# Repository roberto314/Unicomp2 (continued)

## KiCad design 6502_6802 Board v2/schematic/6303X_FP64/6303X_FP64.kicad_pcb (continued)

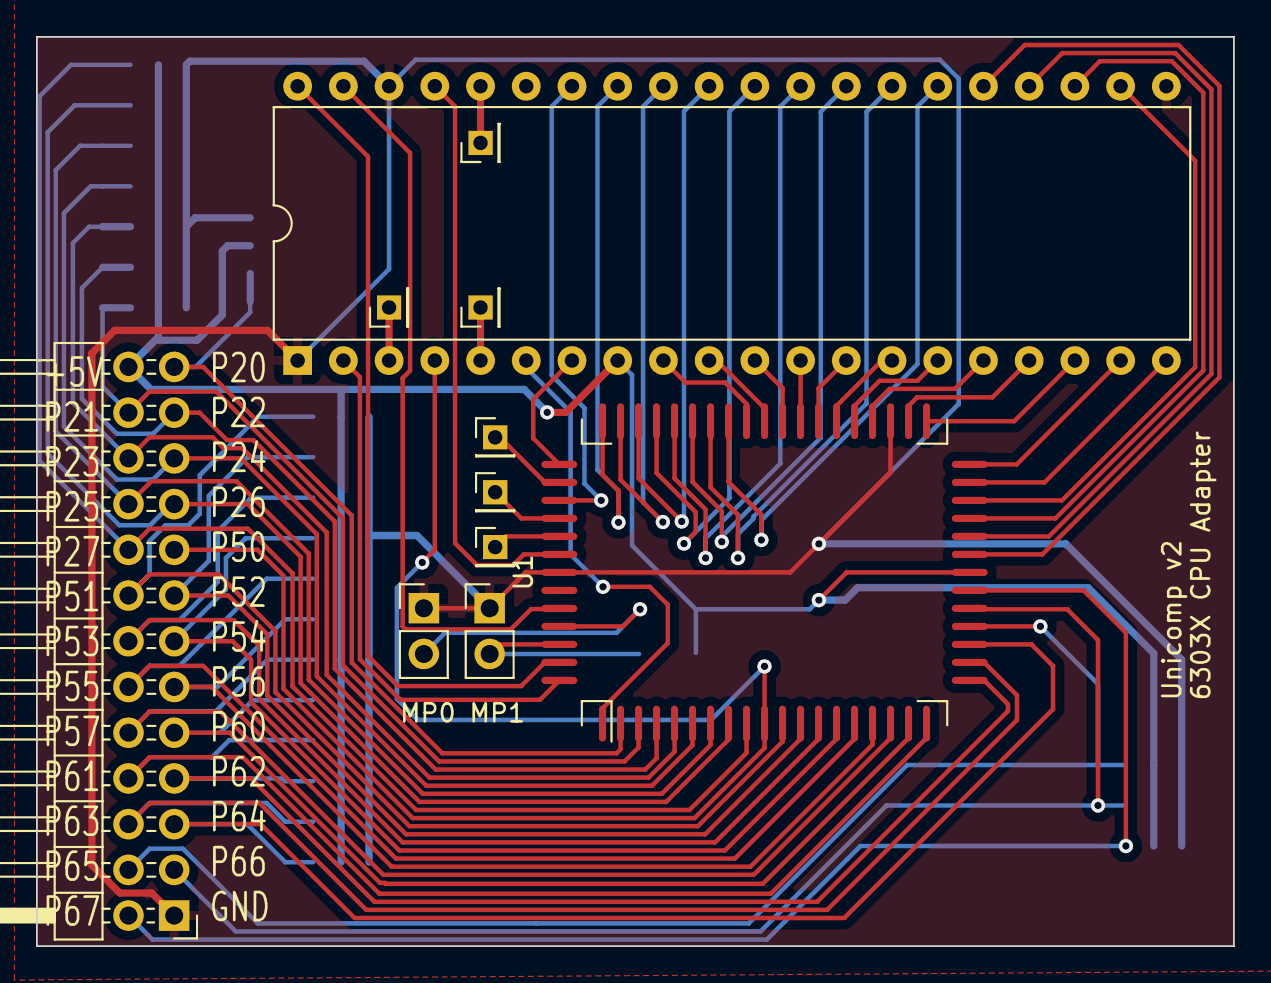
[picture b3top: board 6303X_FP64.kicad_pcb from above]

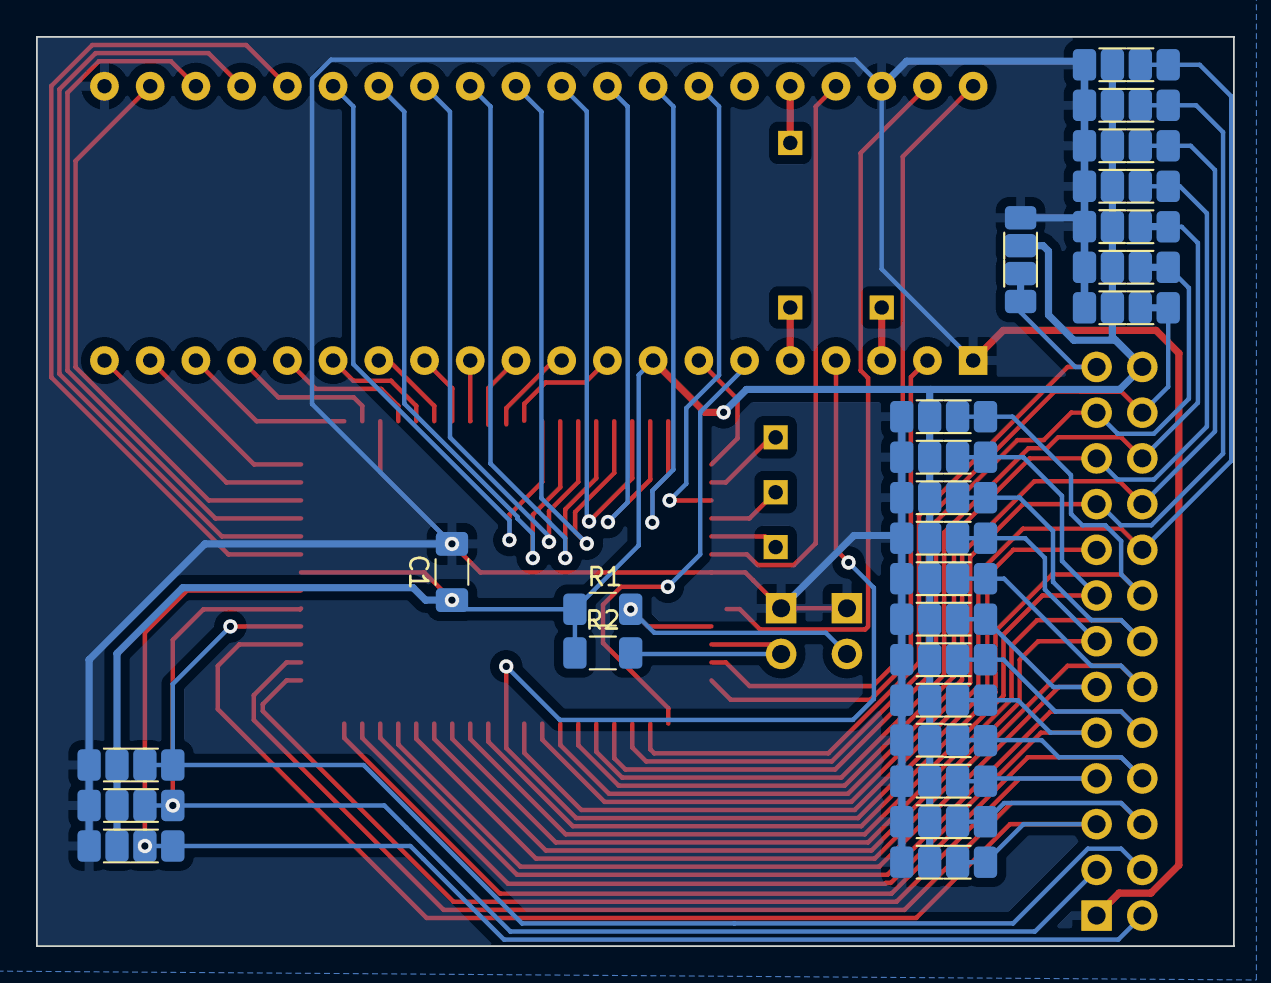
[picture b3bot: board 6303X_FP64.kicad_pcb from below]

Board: 2 copper layers, 66.5 x 50.5 mm, 60 parts (49 on the bottom side), 65 nets.

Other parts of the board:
U3: MC6802; DIP-40_W15.24mm

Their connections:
+5V: U3.8 (VCC); also elsewhere on the board
/A0: U3.9 (A0); also elsewhere on the board
/A1: U3.10 (A1); also elsewhere on the board
/A2: U3.11 (A2); also elsewhere on the board
/A3: U3.12 (A3); also elsewhere on the board
/A4: U3.13 (A4); also elsewhere on the board
/A5: U3.14 (A5); also elsewhere on the board
/A6: U3.15 (A6); also elsewhere on the board
/A7: U3.16 (A7); also elsewhere on the board
/A8: U3.17 (A8); also elsewhere on the board
/A9: U3.18 (A9); also elsewhere on the board
/A10: U3.19 (A10); also elsewhere on the board
/A11: U3.20 (A11); also elsewhere on the board
/A12: U3.22 (A12); also elsewhere on the board
/A13: U3.23 (A13); also elsewhere on the board
/A14: U3.24 (A14); also elsewhere on the board
/A15: U3.25 (A15); also elsewhere on the board
/BA: U3.7 (BA); also elsewhere on the board
/CPUCLK: U3.39 (EXTAL); also elsewhere on the board
/D0: U3.33 (D0); also elsewhere on the board
/D1: U3.32 (D1); also elsewhere on the board
/D2: U3.31 (D2); also elsewhere on the board
/D3: U3.30 (D3); also elsewhere on the board
/D4: U3.29 (D4); also elsewhere on the board
/D5: U3.28 (D5); also elsewhere on the board
/D6: U3.27 (D6); also elsewhere on the board
/D7: U3.26 (D7); also elsewhere on the board
/PHI2: U3.37 (E); also elsewhere on the board
/R/~W: U3.34 (R/~W); also elsewhere on the board
/~HALT: U3.2 (~HALT); also elsewhere on the board
/~IRQ1: U3.4 (~IRQ); also elsewhere on the board
/~NMI: U3.6 (~NMI); also elsewhere on the board
/~RST: U3.40 (~RESET); also elsewhere on the board
GND: U3.1 (VSS), U3.21 (VSS), U3.38 (XTAL); also elsewhere on the board
unnamed 63: U3.3 (MR); also elsewhere on the board
unnamed 64: U3.36 (RE); also elsewhere on the board
unnamed 65: U3.5 (VMA); also elsewhere on the board

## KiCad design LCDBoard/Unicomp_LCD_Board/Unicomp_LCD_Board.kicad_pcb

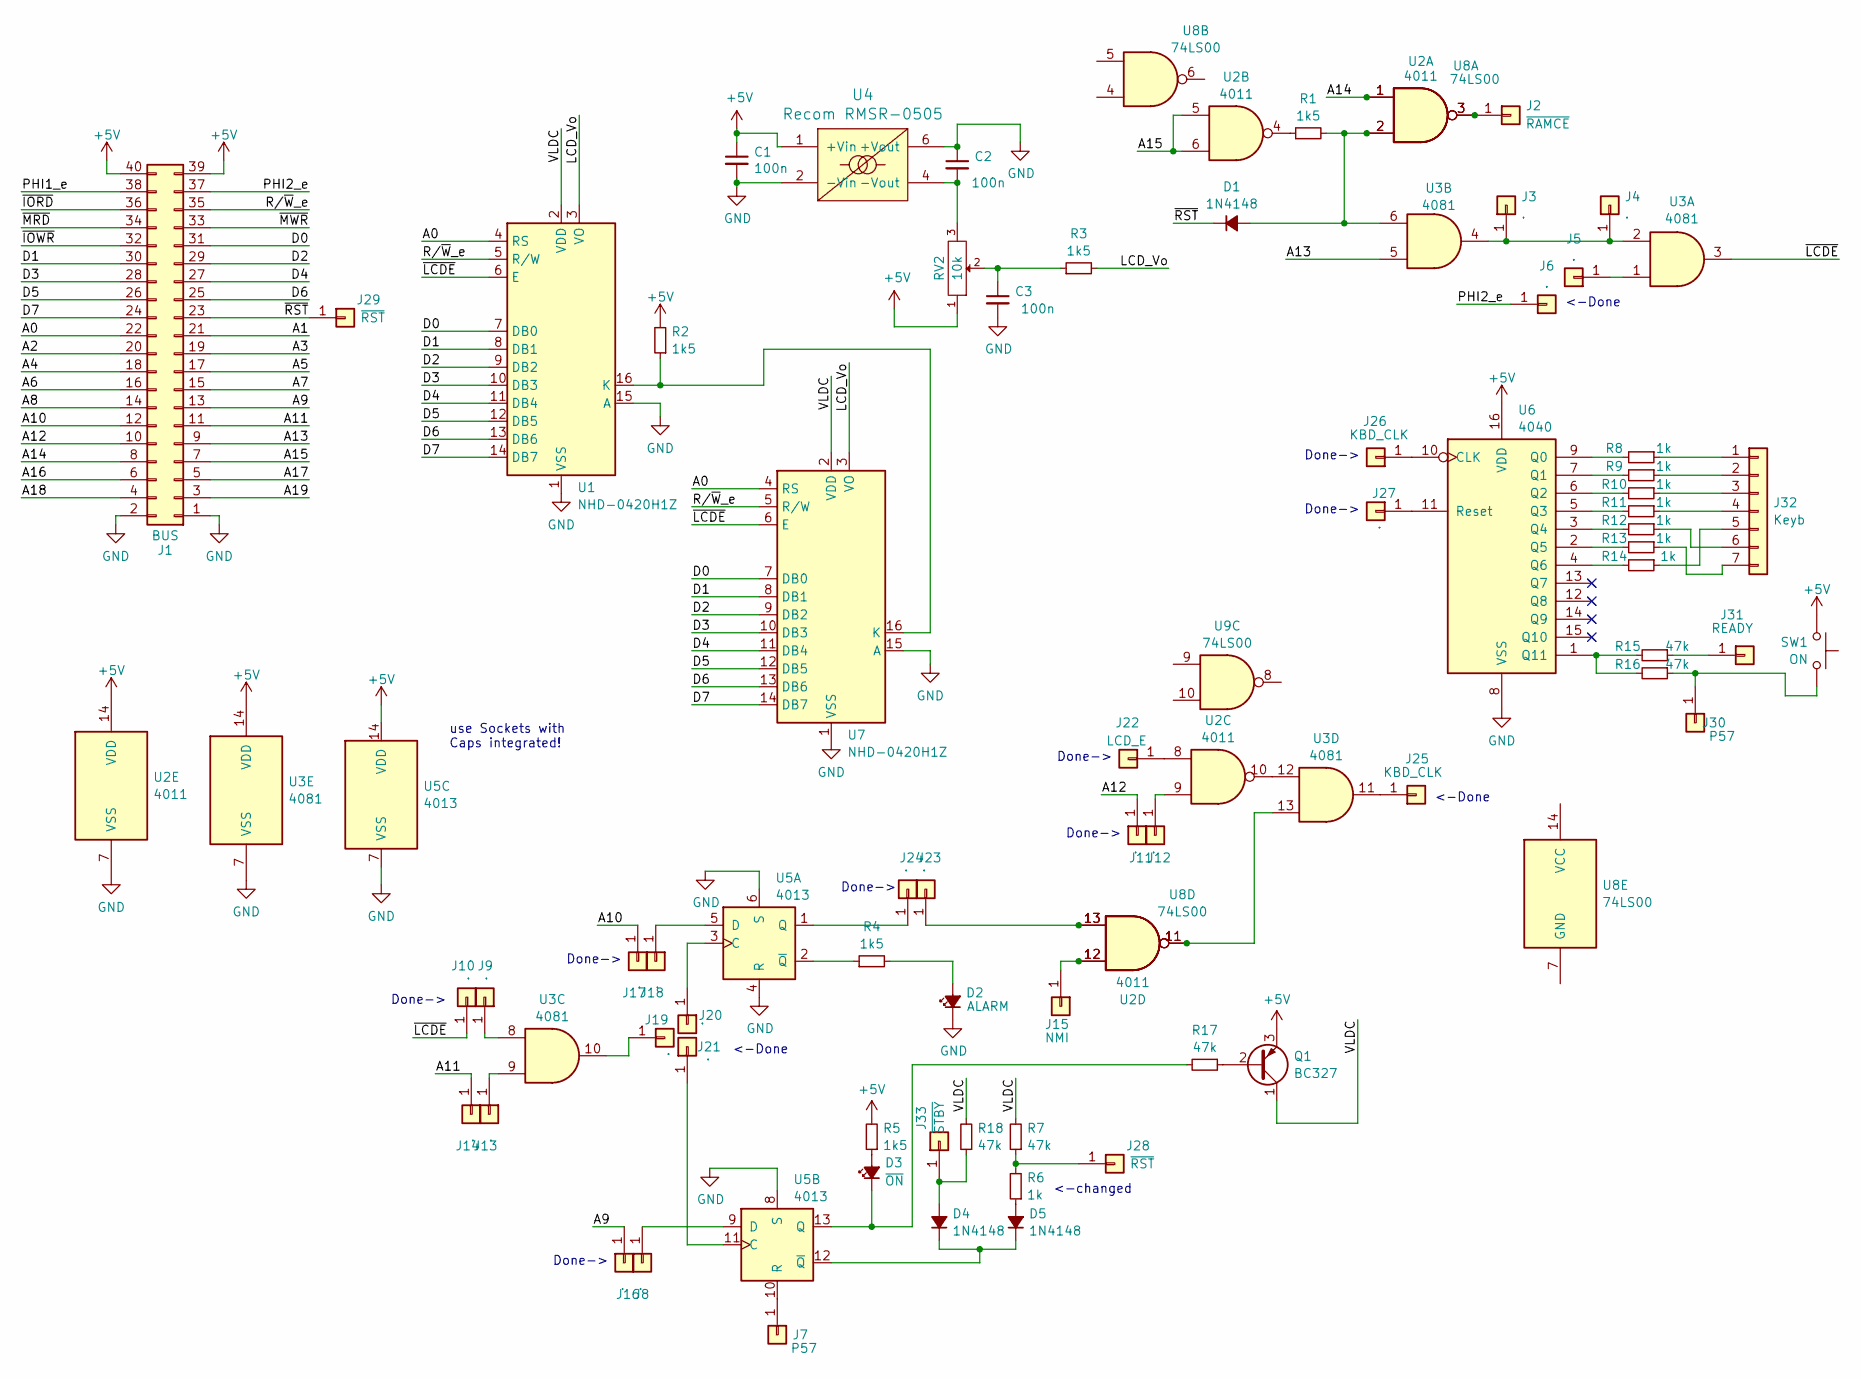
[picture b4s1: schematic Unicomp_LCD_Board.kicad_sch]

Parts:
C1, C2, C3: 100n; C_1206_3216Metric_Pad1.33x1.80mm_HandSolder
D1: 1N4148; D_A-405_P10.16mm_Horizontal
D2: ALARM; LED_D3.0mm
D3: ~{ON}; LED_D3.0mm
D4, D5: 1N4148; D_1206_3216Metric_Pad1.42x1.75mm_HandSolder
J1: BUS; PinHeader_2x20_P2.54mm_Horizontal
J2: ~{RAMCE}; PinHeader_1x01_P2.00mm_Vertical
J3, J4, J5, J6, J8, J9, J10, J11, J12, J13, J14, J16, J17, J18, J19, J20, J21, J23, J24, J27: .; PinHeader_1x01_P2.00mm_Vertical
J7, J30: P57; PinHeader_1x01_P2.00mm_Vertical
J15: NMI; PinHeader_1x01_P2.00mm_Vertical
J22: LCD_E; PinHeader_1x01_P2.00mm_Vertical
J25, J26: KBD_CLK; PinHeader_1x01_P2.00mm_Vertical
J28, J29: ~{RST}; PinHeader_1x01_P2.00mm_Vertical
J31: READY; PinHeader_1x01_P2.00mm_Vertical
J32: Keyb; PinHeader_1x07_P2.54mm_Vertical
J33: ~{STBY}; PinHeader_1x01_P2.00mm_Vertical
Q1: BC327; TO-92_Inline
R1: 1k5; R_Axial_DIN0207_L6.3mm_D2.5mm_P10.16mm_Horizontal
R2, R3, R4, R5: 1k5; R_1206_3216Metric_Pad1.30x1.75mm_HandSolder
R6, R8, R9, R10, R11, R12, R13, R14: 1k; R_1206_3216Metric_Pad1.30x1.75mm_HandSolder
R7, R15, R16, R17, R18: 47k; R_1206_3216Metric_Pad1.30x1.75mm_HandSolder
RV2: 10k; ALPS_RK09
SW1: ON; SW_PUSH_6mm
U1, U7: NHD-0420H1Z; PinSocket_1x16_P2.54mm_Vertical
U2: 4011; DIP-14_W7.62mm_Socket_LongPads
U3: 4081; DIP-14_W7.62mm_Socket_LongPads
U4: Recom RMSR-0505; Converter_DCDC_TRACO_TMR-1-xxxx_Dual_THT
U5: 4013; DIP-14_W7.62mm_Socket_LongPads
U6: 4040; DIP-16_W7.62mm_Socket_LongPads
U8, U9: 74LS00

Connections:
+5V: C1.1, J1.39, J1.40, Q1.3 (E), R2.2, R5.2, RV2.1, SW1.2, U2.14 (VDD), U3.14 (VDD), U4.1 (+Vin), U5.14 (VDD), U6.16 (VDD)
/A0: J1.22, U1.4 (RS), U7.4 (RS)
/A1: J1.21
/A2: J1.20
/A3: J1.19
/A4: J1.18
/A5: J1.17
/A6: J1.16
/A7: J1.15
/A8: J1.14
/A9: J1.13, J16.1
/A10: J1.12, J17.1
/A11: J1.11, J14.1
/A12: J1.10, J11.1
/A13: J1.9, U3.5
/A14: J1.8, U2.1, U8.1
/A15: J1.7, U2.5, U2.6
/A16: J1.6
/A17: J1.5
/A18: J1.4
/A19: J1.3
/D0: J1.31, U1.7 (DB0), U7.7 (DB0)
/D1: J1.30, U1.8 (DB1), U7.8 (DB1)
/D2: J1.29, U1.9 (DB2), U7.9 (DB2)
/D3: J1.28, U1.10 (DB3), U7.10 (DB3)
/D4: J1.27, U1.11 (DB4), U7.11 (DB4)
/D5: J1.26, U1.12 (DB5), U7.12 (DB5)
/D6: J1.25, U1.13 (DB6), U7.13 (DB6)
/D7: J1.24, U1.14 (DB7), U7.14 (DB7)
/LCD_Vo: R3.2, U1.3 (VO), U7.3 (VO)
/PHI1_e: J1.38
/PHI2_e: J1.37, J6.1
/R/~W_e: J1.35, U1.5 (R/W), U7.5 (R/W)
/VLDC: Q1.1 (C), R7.2, R18.2, U1.2 (VDD), U7.2 (VDD)
/~IORD: J1.36
/~IOWR: J1.32
/~LCDE: J10.1, U1.6 (E), U3.3, U7.6 (E)
/~MRD: J1.34
/~MWR: J1.33
/~RST: D1.1 (K), J1.23, J29.1
GND: C1.2, C2.1, C3.2, D2.1 (K), J1.1, J1.2, U1.1 (VSS), U1.15 (A), U2.7 (VSS), U3.7 (VSS), U4.2 (-Vin), U4.6 (+Vout), U5.4 (R), U5.6 (S), U5.7 (VSS), U5.8 (S), U6.8 (VSS), U7.1 (VSS), U7.15 (A)
unnamed: C3.1, R3.1, RV2.2
unnamed: D1.2 (A), R1.2, U2.2, U3.6, U8.2
unnamed: D2.2 (A), R4.2
unnamed: D3.2 (A), R5.1
unnamed: D3.1 (K), R17.2, U5.13 (Q)
unnamed: D4.2 (A), J33.1, R18.1
unnamed: D4.1 (K), D5.1 (K), U5.12 (~Q)
unnamed: D5.2 (A), R6.1
unnamed: J2.1, U2.3, U8.3
unnamed: J3.1, J4.1, U3.2, U3.4
unnamed: J5.1, U3.1
unnamed: J7.1, U5.10 (R)
unnamed: J8.1, U5.9 (D)
unnamed: J9.1, U3.8
unnamed: J12.1, U2.9
unnamed: J13.1, U3.9
unnamed: J15.1, U2.12, U8.12
unnamed: J18.1, U5.5 (D)
unnamed: J19.1, U3.10
unnamed: J20.1, U5.3 (C)
unnamed: J21.1, U5.11 (C)
unnamed: J22.1, U2.8
unnamed: J23.1, U2.13, U8.13
unnamed: J24.1, U5.1 (Q)
unnamed: J25.1, U3.11
unnamed: J26.1, U6.10 (CLK)
unnamed: J27.1, U6.11 (Reset)
unnamed: J28.1, R6.2, R7.1
unnamed: J30.1, R16.1, SW1.1
unnamed: J31.1, R15.1
unnamed: J32.1, R8.1
unnamed: J32.2, R9.1
unnamed: J32.3, R10.1
unnamed: J32.4, R11.1
unnamed: J32.5, R14.1
unnamed: J32.6, R12.1
unnamed: J32.7, R13.1
unnamed: Q1.2 (B), R17.1
unnamed: R1.1, U2.4
unnamed: R2.1, U1.16 (K), U7.16 (K)
unnamed: U2.10, U3.12
unnamed: U2.11, U3.13, U8.11
unnamed: C2.2, RV2.3, U4.4 (-Vout)
unnamed: R4.1, U5.2 (~Q)
unnamed: R8.2, U6.9 (Q0)
unnamed: R9.2, U6.7 (Q1)
unnamed: R10.2, U6.6 (Q2)
unnamed: R11.2, U6.5 (Q3)
unnamed: R12.2, U6.3 (Q4)
unnamed: R13.2, U6.2 (Q5)
unnamed: R14.2, U6.4 (Q6)
unnamed: R15.2, R16.2, U6.1 (Q11)

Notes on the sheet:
<-Done
Done->
use Sockets with Caps integrated!
<-changed

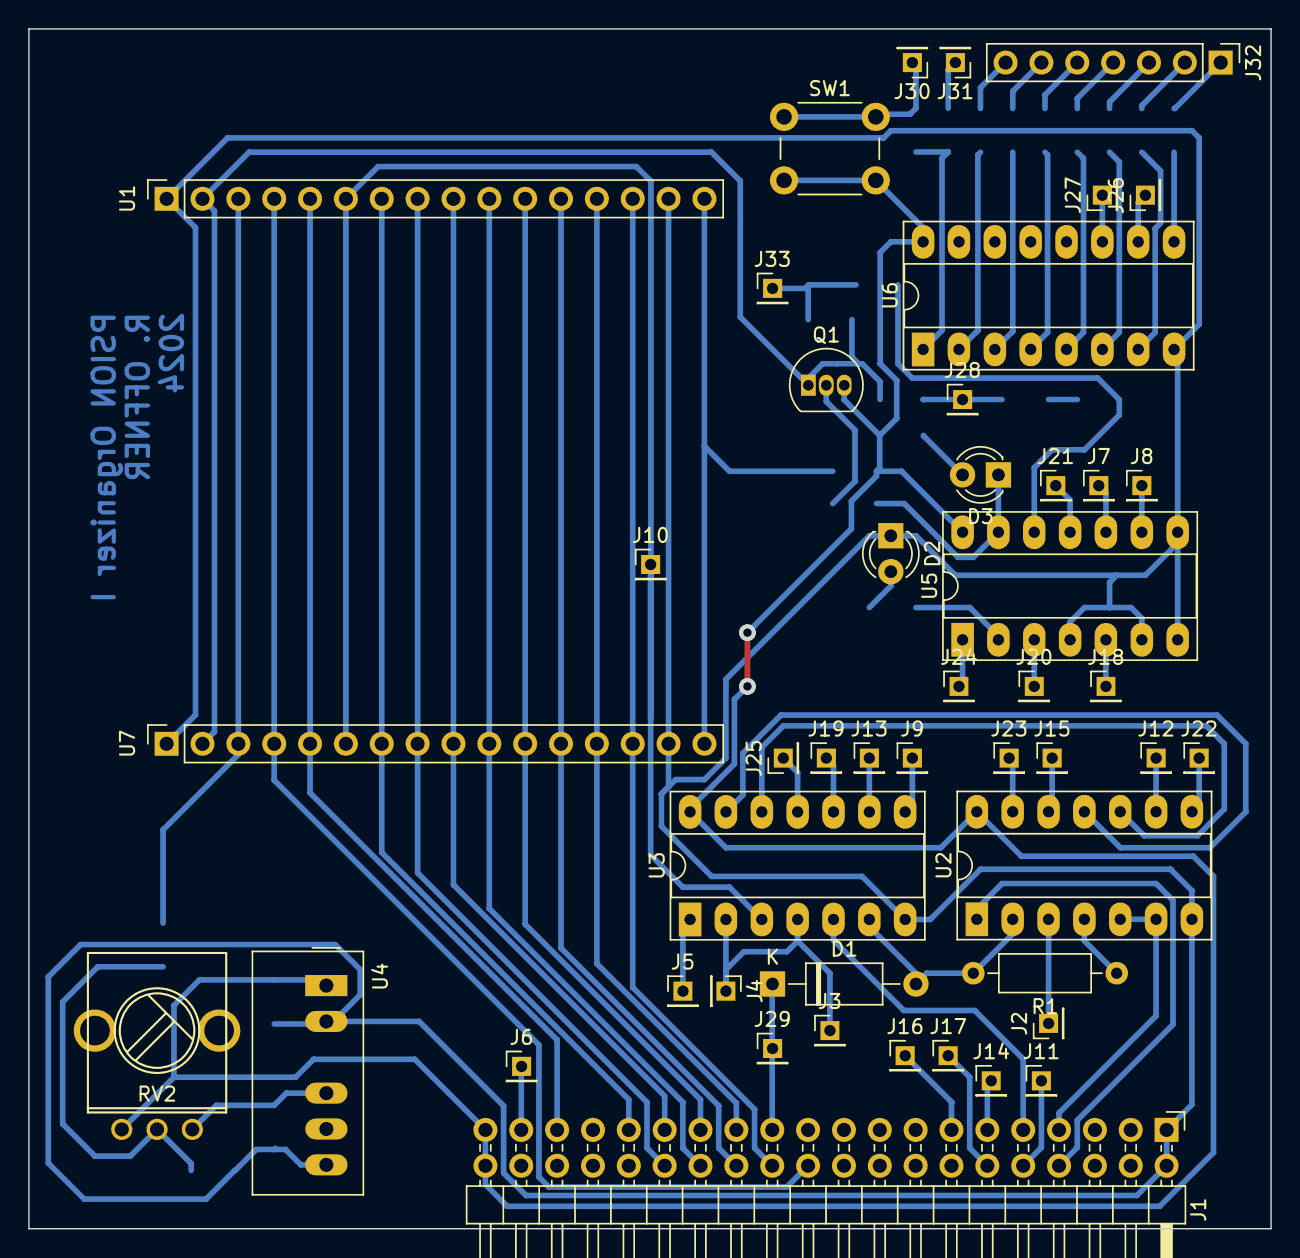
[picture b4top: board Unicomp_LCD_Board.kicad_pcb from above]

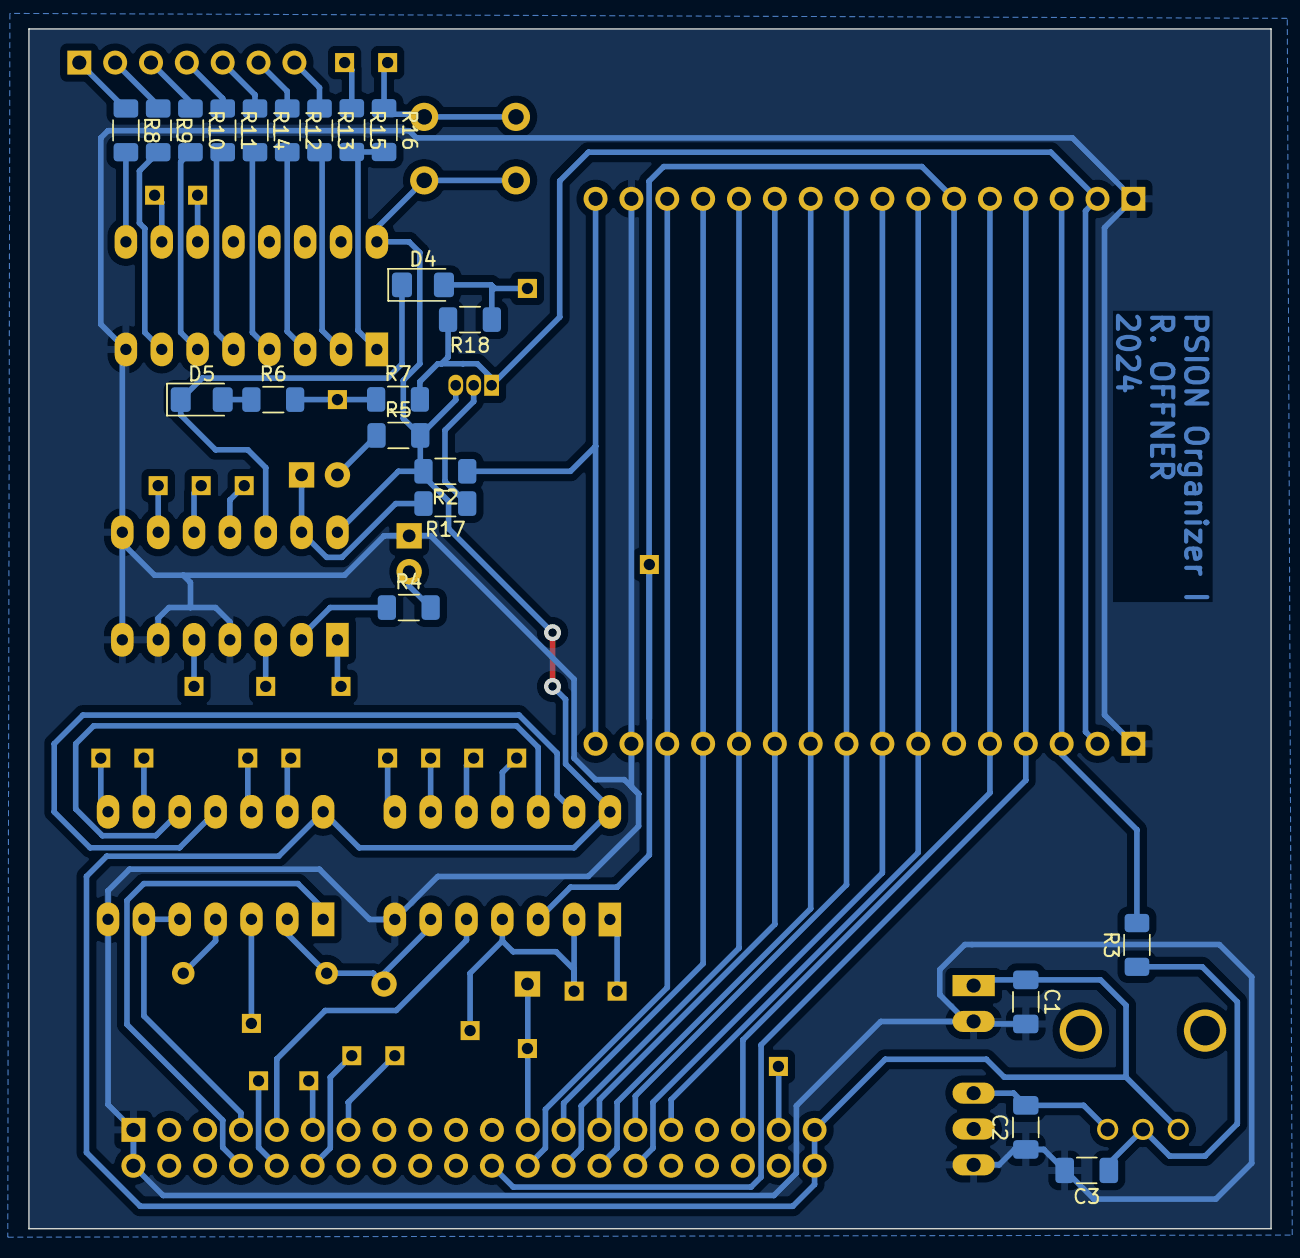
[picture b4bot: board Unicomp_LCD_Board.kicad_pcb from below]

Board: 2 copper layers, 88.0 x 85.0 mm, 69 parts (22 on the bottom side), 76 nets.

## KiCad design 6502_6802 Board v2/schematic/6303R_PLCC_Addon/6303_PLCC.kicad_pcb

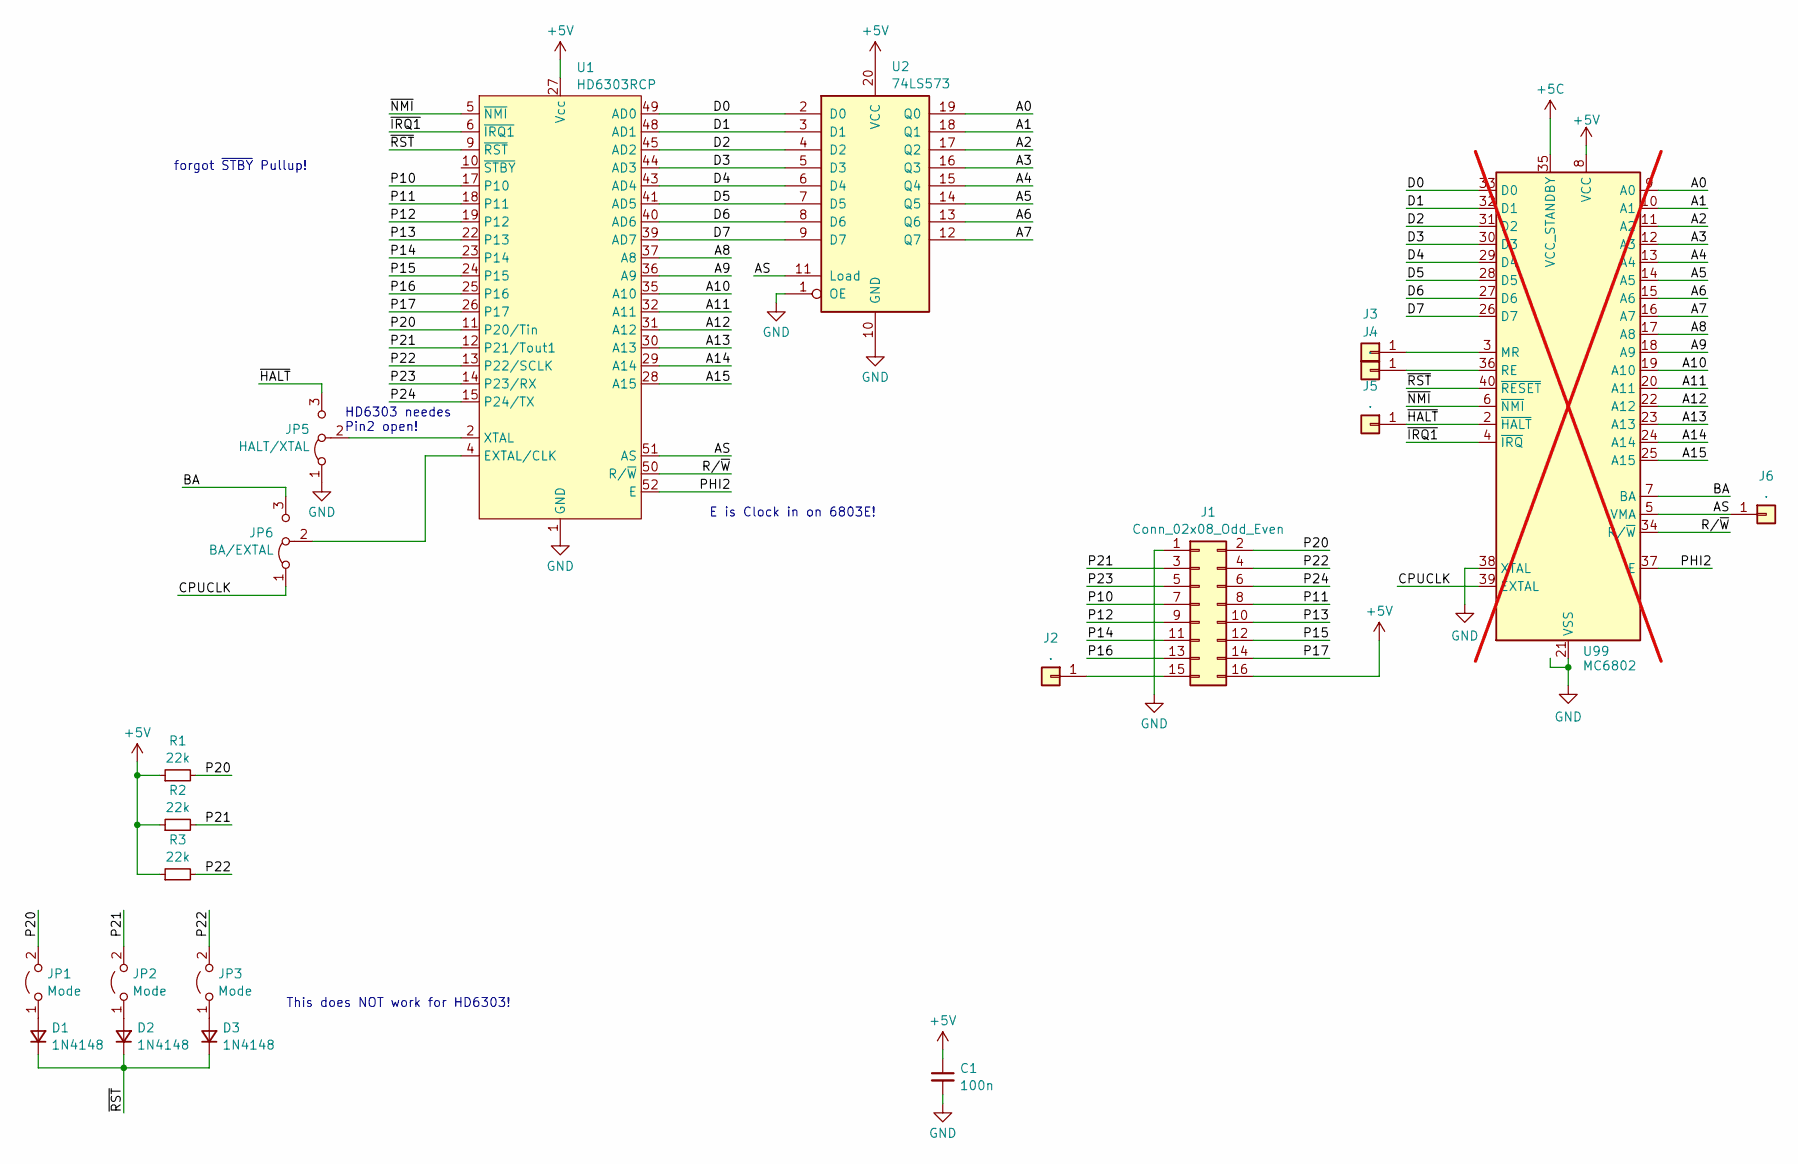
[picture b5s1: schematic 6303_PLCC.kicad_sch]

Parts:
C1: 100n; C_1206_3216Metric_Pad1.33x1.80mm_HandSolder
D1, D2, D3: 1N4148; D_1206_3216Metric_Pad1.42x1.75mm_HandSolder
J1: Conn_02x08_Odd_Even; PinHeader_2x08_P2.54mm_Horizontal
J2, J3, J4, J5, J6: .; PinHeader_1x01_P2.00mm_Vertical
JP1, JP2, JP3: Mode; PinHeader_1x02_P2.54mm_Vertical
JP5: HALT/XTAL; PinHeader_1x03_P2.54mm_Vertical
JP6: BA/EXTAL; PinHeader_1x03_P2.54mm_Vertical
R1, R2, R3: 22k; R_1206_3216Metric_Pad1.30x1.75mm_HandSolder
U1: HD6303RCP; PLCC-52_SMD-Socket
U2: 74LS573; DIP-20_W7.62mm_Socket_LongPads
U99: MC6802; DIP-40_W15.24mm; not fitted

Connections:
+5V: C1.1, J1.16, R1.1, R2.1, R3.1, U1.27 (Vcc), U2.20 (VCC); also elsewhere on the board
/A0: U2.19 (Q0); also elsewhere on the board
/A1: U2.18 (Q1); also elsewhere on the board
/A2: U2.17 (Q2); also elsewhere on the board
/A3: U2.16 (Q3); also elsewhere on the board
/A4: U2.15 (Q4); also elsewhere on the board
/A5: U2.14 (Q5); also elsewhere on the board
/A6: U2.13 (Q6); also elsewhere on the board
/A7: U2.12 (Q7); also elsewhere on the board
/A8: U1.37 (A8); also elsewhere on the board
/A9: U1.36 (A9); also elsewhere on the board
/A10: U1.35 (A10); also elsewhere on the board
/A11: U1.32 (A11); also elsewhere on the board
/A12: U1.31 (A12); also elsewhere on the board
/A13: U1.30 (A13); also elsewhere on the board
/A14: U1.29 (A14); also elsewhere on the board
/A15: U1.28 (A15); also elsewhere on the board
/AS: J6.1, U1.51 (AS), U2.11 (Load); also elsewhere on the board
/BA: JP6.3 (B); also elsewhere on the board
/CPUCLK: JP6.1 (A); also elsewhere on the board
/D0: U1.49 (AD0), U2.2 (D0); also elsewhere on the board
/D1: U1.48 (AD1), U2.3 (D1); also elsewhere on the board
/D2: U1.45 (AD2), U2.4 (D2); also elsewhere on the board
/D3: U1.44 (AD3), U2.5 (D3); also elsewhere on the board
/D4: U1.43 (AD4), U2.6 (D4); also elsewhere on the board
/D5: U1.41 (AD5), U2.7 (D5); also elsewhere on the board
/D6: U1.40 (AD6), U2.8 (D6); also elsewhere on the board
/D7: U1.39 (AD7), U2.9 (D7); also elsewhere on the board
/P10: J1.7, U1.17 (P10)
/P11: J1.8, U1.18 (P11)
/P12: J1.9, U1.19 (P12)
/P13: J1.10, U1.22 (P13)
/P14: J1.11, U1.23 (P14)
/P15: J1.12, U1.24 (P15)
/P16: J1.13, U1.25 (P16)
/P17: J1.14, U1.26 (P17)
/P20: J1.2, JP1.2 (B), R1.2, U1.11 (P20/Tin)
/P21: J1.3, JP2.2 (B), R2.2, U1.12 (P21/Tout1)
/P22: J1.4, JP3.2 (B), R3.2, U1.13 (P22/SCLK)
/P23: J1.5, U1.14 (P23/RX)
/P24: J1.6, U1.15 (P24/TX)
/PHI2: U1.52 (E); also elsewhere on the board
/R/~W: U1.50 (R/~W); also elsewhere on the board
/~HALT: J5.1, JP5.3 (B); also elsewhere on the board
/~IRQ1: U1.6 (~IRQ1); also elsewhere on the board
/~NMI: U1.5 (~NMI); also elsewhere on the board
/~RST: D1.1 (K), D2.1 (K), D3.1 (K), U1.9 (~RST); also elsewhere on the board
GND: C1.2, J1.1, JP5.1 (A), U1.1 (GND), U2.1 (OE), U2.10 (GND); also elsewhere on the board
unnamed: D1.2 (A), JP1.1 (A)
unnamed: D2.2 (A), JP2.1 (A)
unnamed: D3.2 (A), JP3.1 (A)
unnamed: J1.15, J2.1
unnamed 53: J3.1; also elsewhere on the board
unnamed 54: J4.1; also elsewhere on the board
unnamed: JP5.2 (C), U1.2 (XTAL)
unnamed: JP6.2 (C), U1.4 (EXTAL/CLK)

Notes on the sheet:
forgot ~{STBY} Pullup!
This does NOT work for HD6303!
E is Clock in on 6803E!
HD6303 needes Pin2 open!

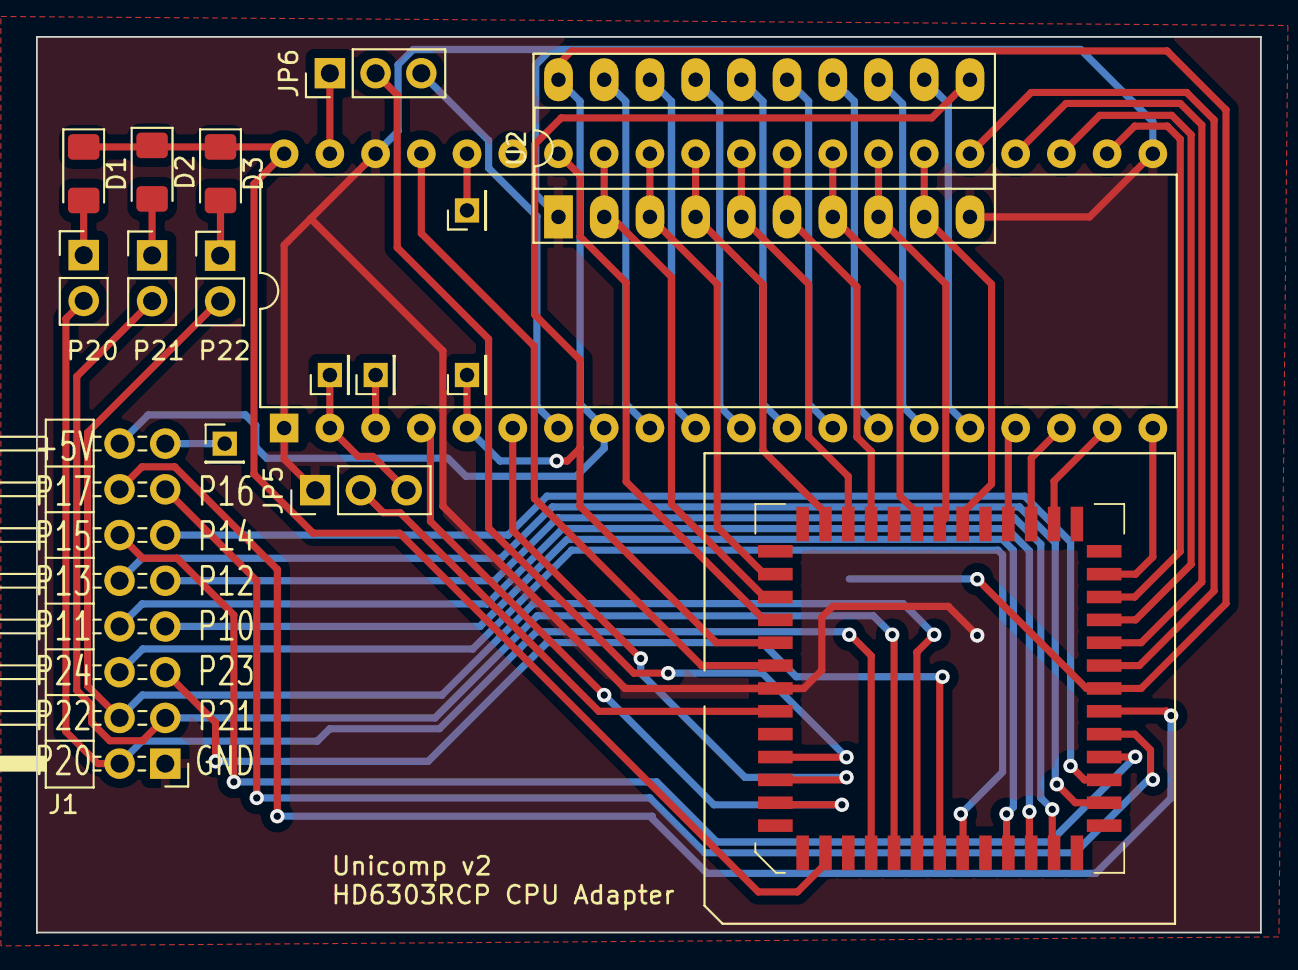
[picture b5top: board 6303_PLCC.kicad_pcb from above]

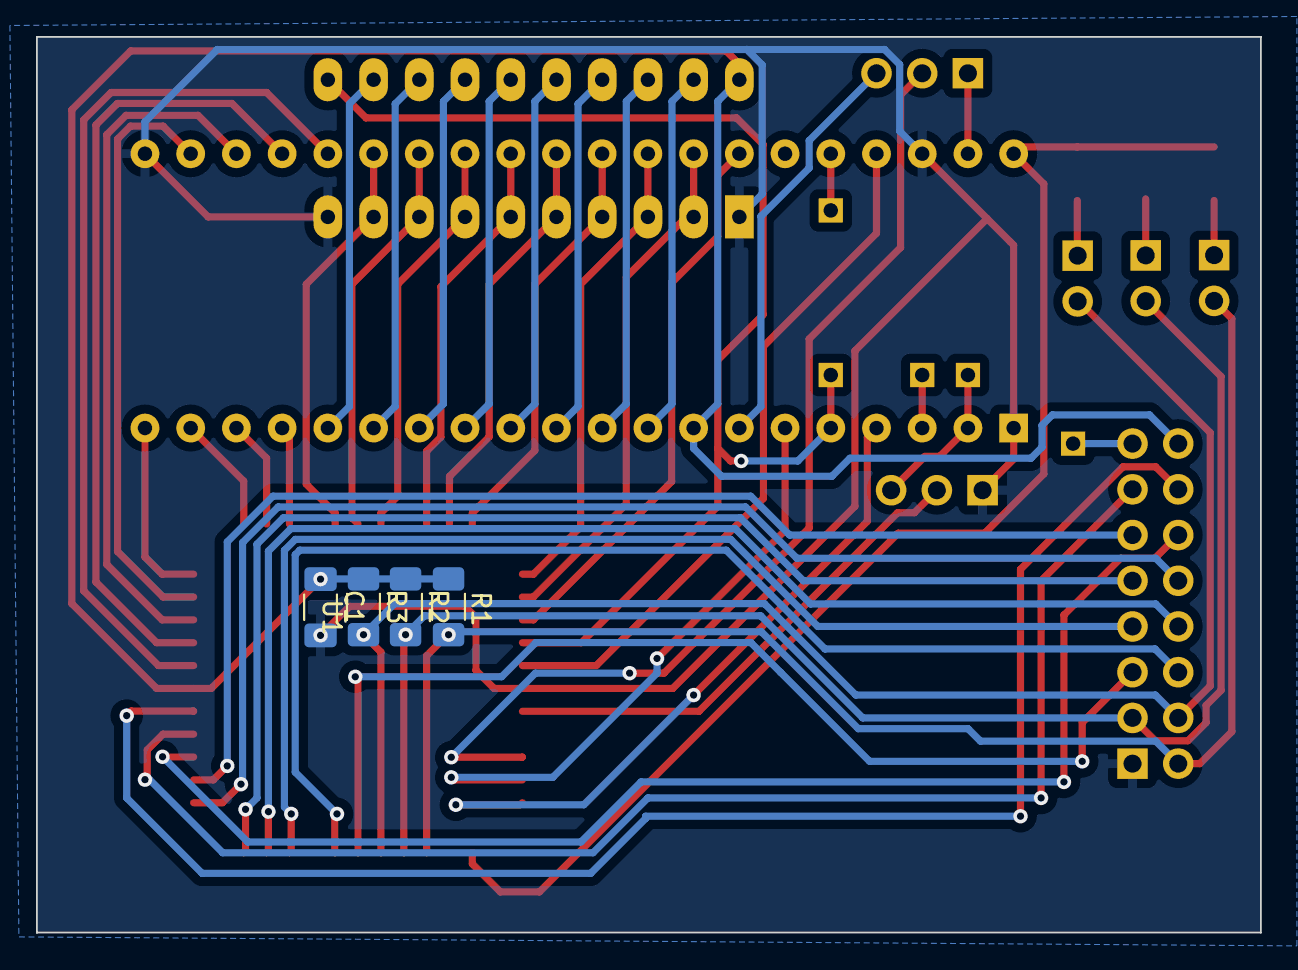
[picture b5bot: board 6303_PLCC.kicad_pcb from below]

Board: 2 copper layers, 68.0 x 49.8 mm, 21 parts (4 on the bottom side), 56 nets.

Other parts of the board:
U3: MC6802; DIP-40_W15.24mm

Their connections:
+5V: U3.8 (VCC); also elsewhere on the board
/A0: U3.9 (A0); also elsewhere on the board
/A1: U3.10 (A1); also elsewhere on the board
/A2: U3.11 (A2); also elsewhere on the board
/A3: U3.12 (A3); also elsewhere on the board
/A4: U3.13 (A4); also elsewhere on the board
/A5: U3.14 (A5); also elsewhere on the board
/A6: U3.15 (A6); also elsewhere on the board
/A7: U3.16 (A7); also elsewhere on the board
/A8: U3.17 (A8); also elsewhere on the board
/A9: U3.18 (A9); also elsewhere on the board
/A10: U3.19 (A10); also elsewhere on the board
/A11: U3.20 (A11); also elsewhere on the board
/A12: U3.22 (A12); also elsewhere on the board
/A13: U3.23 (A13); also elsewhere on the board
/A14: U3.24 (A14); also elsewhere on the board
/A15: U3.25 (A15); also elsewhere on the board
/AS: U3.5 (VMA); also elsewhere on the board
/BA: U3.7 (BA); also elsewhere on the board
/CPUCLK: U3.39 (EXTAL); also elsewhere on the board
/D0: U3.33 (D0); also elsewhere on the board
/D1: U3.32 (D1); also elsewhere on the board
/D2: U3.31 (D2); also elsewhere on the board
/D3: U3.30 (D3); also elsewhere on the board
/D4: U3.29 (D4); also elsewhere on the board
/D5: U3.28 (D5); also elsewhere on the board
/D6: U3.27 (D6); also elsewhere on the board
/D7: U3.26 (D7); also elsewhere on the board
/PHI2: U3.37 (E); also elsewhere on the board
/R/~W: U3.34 (R/~W); also elsewhere on the board
/~HALT: U3.2 (~HALT); also elsewhere on the board
/~IRQ1: U3.4 (~IRQ); also elsewhere on the board
/~NMI: U3.6 (~NMI); also elsewhere on the board
/~RST: U3.40 (~RESET); also elsewhere on the board
GND: U3.1 (VSS), U3.21 (VSS), U3.38 (XTAL); also elsewhere on the board
unnamed 53: U3.3 (MR); also elsewhere on the board
unnamed 54: U3.36 (RE); also elsewhere on the board
